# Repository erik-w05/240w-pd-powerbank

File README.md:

!WORK IN PROGRESS, NOT YET READY FOR PRODUCTION!

# 240w-pd-powerbank
A 2-14S USB-C powerbank Hardware and Software Project, which is capable of charging and discharging at 48V@5A, which is the maximum power the USB-C PD 3.2 EPR standard supports.

The design is based on the BQ25756 4-Switch (bidirectional) Buck-Boost Charge-IC and the TPS26750 USB-C PD-Controller. Even though both of these Chips could work together standalone, the RP2354 MCU is used to control the PD-negotiation and Charger-Operation, to expand the functionality.

# Features

PCB:

- 100x80mm Board Size with 4x M3 Mounting Holes

- 6 Layer Board with sensitive signals on Layer 1 and 6

- 2oz outer copper and 1oz Inner Copper possible for improved thermal performance

Power:

- USB-PD EPR 3.2 Protocol with 48V/5A, PPS and AVS

- Dead-battery support (Powerup from 5V)

- BQ25756 4-Switch Buck-Boost Controller capable of bidirectional Buck/Boost

- 2S-14S battery support, recommended for 48V@5A PD EPR is 8S-14S (14S is most efficient)

- 5A input current through USB-C and 10A discharge current max from the battery

- LMR38010 Buck Converter that generates 3.3V from 4.2-58.8V

- 7V boost converter for Gate Drive Supply

Human-Machine Interface (HMI)
- SPI Header for one Display
- 2x Buttons and 1x Rotary Encoder for User Interface Navigation
- 1x Neopixel LED for Status Indication
- Buzzer for User Feedback and Alerting

# Cost

On JLCPCB the board itself costs about 100€/5 Pieces and the components are about 100€ per board. If you want to get the board assembled, the cost will be very high. The bulk of the cost comes from assembly because of the use of mostly non-basic parts.

# My Motivation:

My old powerbank broke a couple of months ago and I always wanted to make one myself. And I also noticed, that such an Product didn't yet exist on the market, so I decided to make the first.

Inspiration:

Thanks for Theo Heng for giving me the idea and orientation on how to implement it.
https://github.com/theohg/PD240W

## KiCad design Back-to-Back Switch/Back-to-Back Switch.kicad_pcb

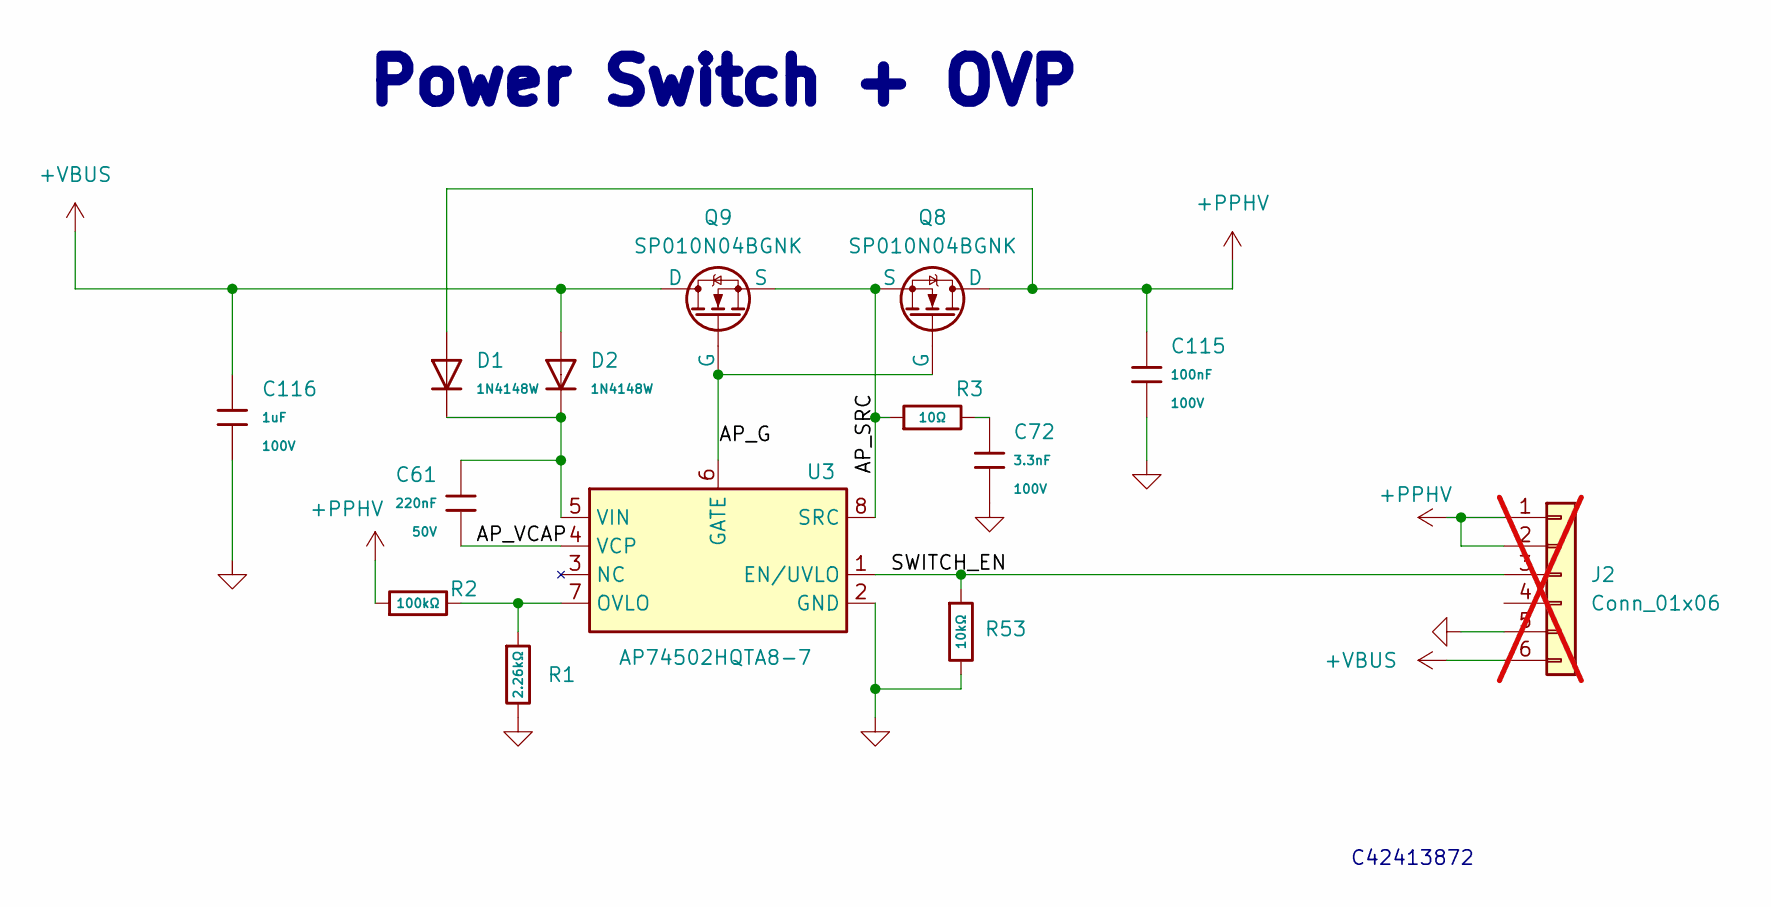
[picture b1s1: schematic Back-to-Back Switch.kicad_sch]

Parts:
C61: 220nF; C_0603_1608Metric; Voltage Rated 50V; Tolerance ±10%; Manufacturer Part Number CC0603KRX7R9BB224; LCSC C107083
C72: 3.3nF; C_0603_1608Metric; Voltage Rated 100V; Tolerance ±10%; LCSC C388015
C115: 100nF; C_0603_1608Metric; Voltage Rated 100V; Tolerance ±10%; LCSC C15725
C116: 1uF; C_0805_2012Metric; Voltage Rated 100V; Tolerance ±10%; LCSC C5370002
D1, D2: 1N4148W; D_SOD-123; Forward Voltage (Vf@If) 1.25V@150mA; Reverse Voltage (Vr) 100V; Part 1N4148W; LCSC C7420318
J2: Conn_01x06; PinHeader_1x06_P2.54mm_Vertical; not fitted
Q8, Q9: SP010N04BGNK; PDFN-8_L5.8-W5.0-P1.27-LS6.1-BL; LCSC C22466791
R1: 2.26kΩ; R_0603; Overload Voltage (Max) 75V; Tolerance ±1%
R2: 100kΩ; R_0603; Overload Voltage (Max) 75V; Tolerance ±1%; Part 0603WAF1003T5E; LCSC C25803
R3: 10Ω; R_0603; Overload Voltage (Max) 75V; Tolerance ±1%; Part 0603WAF100JT5E; LCSC C22859
R53: 10kΩ; R_0603_1608Metric; Overload Voltage (Max) 75V; Tolerance ±1%; LCSC C25804
U3: AP74502HQTA8-7; AP74502HQTA87

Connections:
+PPHV: C115.1, D1.2, J2.1, J2.2, Q8.5 (D), R2.1
+VBUS: C116.1, D2.2, J2.6, Q9.5 (D)
/AP_G: Q8.4 (G), Q9.4 (G), U3.6 (GATE)
/AP_SRC: Q8.1 (S), Q8.2 (S), Q8.3 (S), Q9.1 (S), Q9.2 (S), Q9.3 (S), R3.1, U3.8 (SRC)
/AP_VCAP: C61.2, U3.4 (VCP)
/SWITCH_EN: J2.3, R53.1, U3.1 (EN/UVLO)
GND: C72.2, C115.2, C116.2, J2.5, R1.2, R53.2, U3.2 (GND)
unnamed: C72.1, R3.2
unnamed: R1.1, R2.2, U3.7 (OVLO)
unnamed: C61.1, D1.1, D2.1, U3.5 (VIN)

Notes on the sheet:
C42413872
Power Switch + OVP

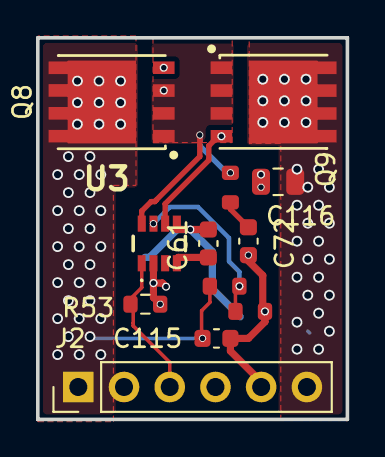
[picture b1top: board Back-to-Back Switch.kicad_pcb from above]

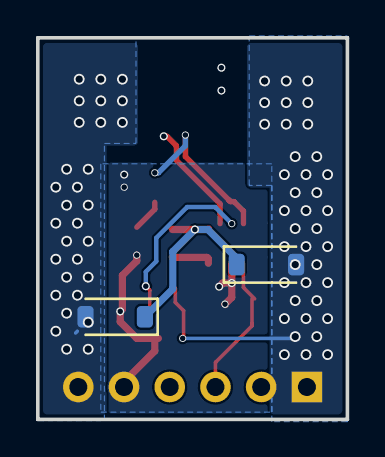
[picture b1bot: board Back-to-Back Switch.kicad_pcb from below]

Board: 4 copper layers, 17.2 x 21.2 mm, 14 parts (2 on the bottom side), 10 nets.

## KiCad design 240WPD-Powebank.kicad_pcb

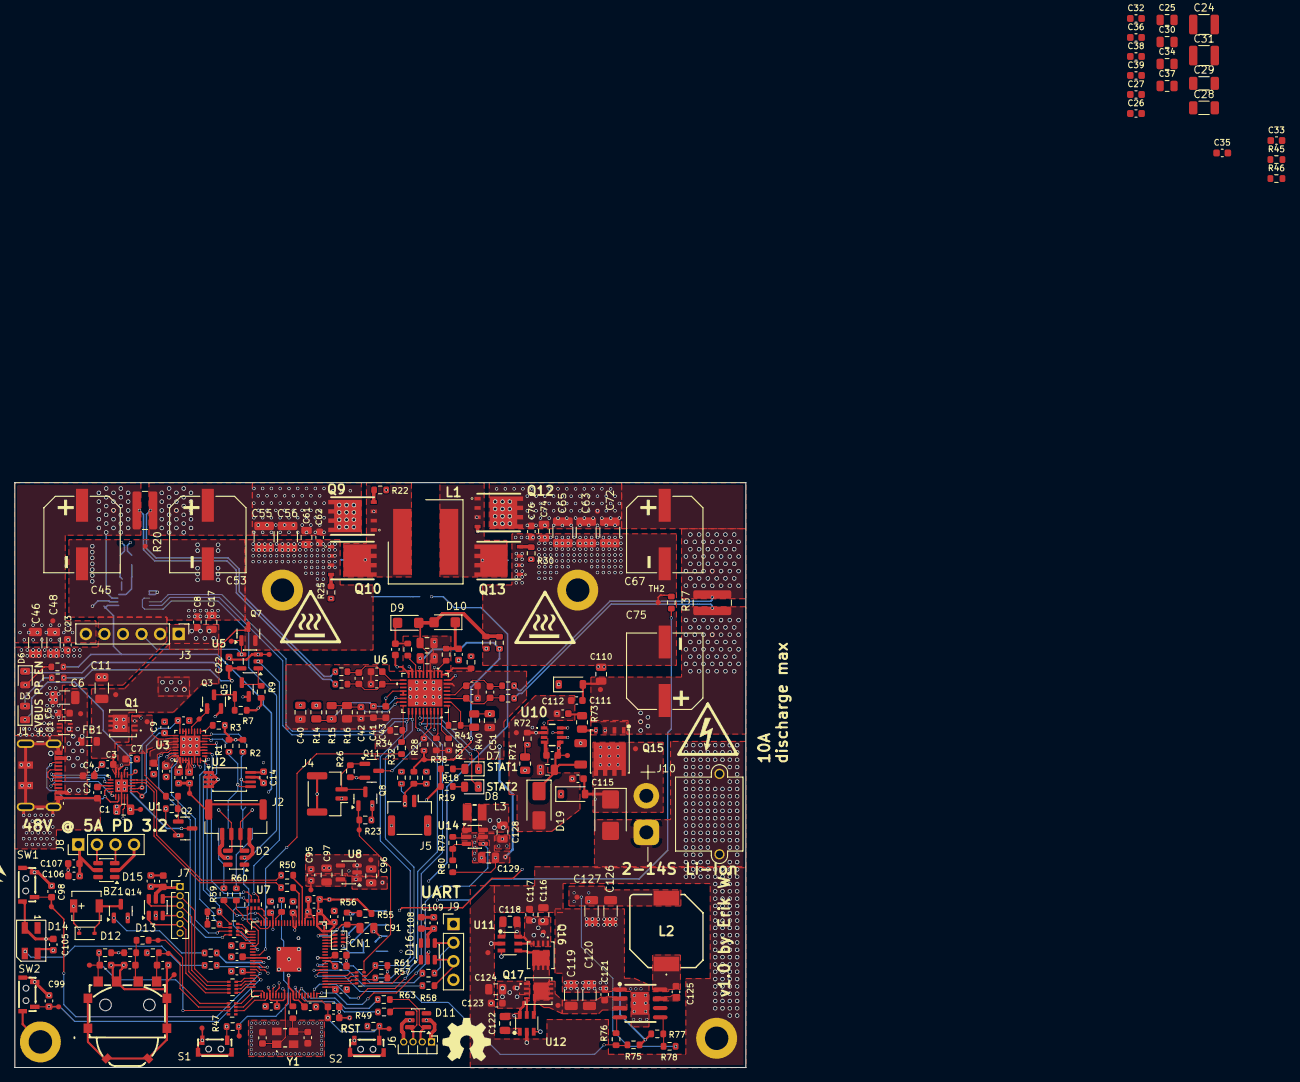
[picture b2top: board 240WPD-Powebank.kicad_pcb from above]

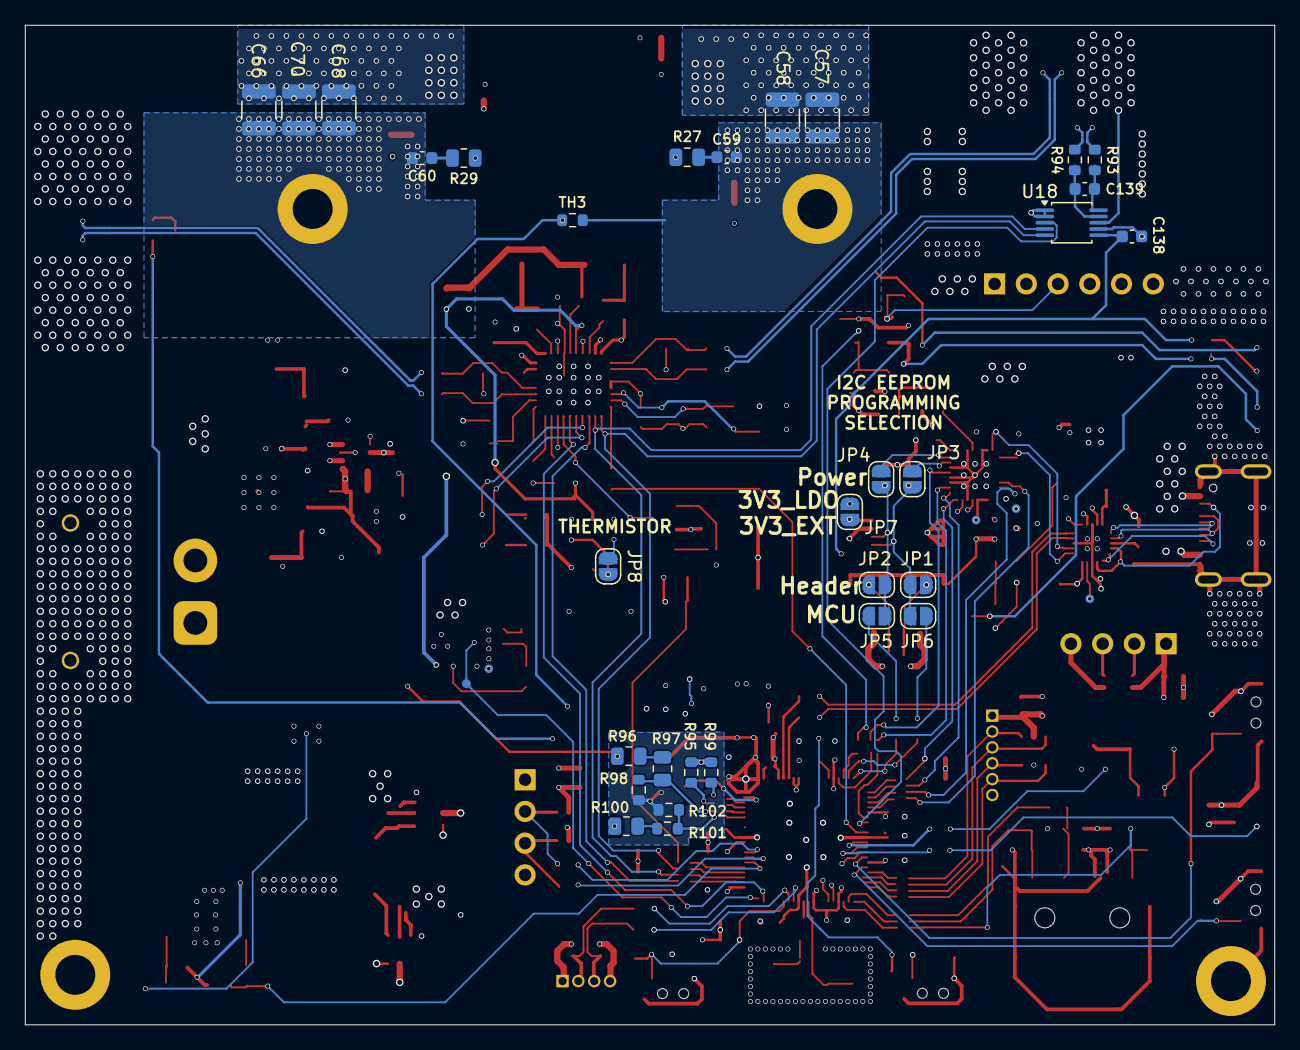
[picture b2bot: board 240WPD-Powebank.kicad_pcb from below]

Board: 6 copper layers, 100.0 x 80.0 mm, 362 parts (43 on the bottom side), 190 nets.

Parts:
BZ1: Buzzer; BUZ-SMD_L4.0-W4.0-P3.50-L
C1, C17, C25, C40, C51, C61, C74, C96, C97, C110, C114, C116, C118, C122, C124: 1uF; C_0805_2012Metric
C2, C3, C7, C8, C14, C22, C23, C32, C41, C42, C43, C49, C52, C54, C62, C64, C69, C73, C79, C80, C81, C83, C84, C85, C87, C89, C90, C92, C93, C94, C98, C99, C101, C102, C103, C104, C105, C107, C109, C111, C115, C117, C121, C123, C125, C138, C139: 100nF; C_0603_1608Metric
C4, C5: 10nF; C_0603_1608Metric
C6, C11, C29, C46, C48, C119, C120: 4.7uF; C_1206_3216Metric
C9, C10, C27: 220pF; C_0603_1608Metric
C12, C13, C15, C16, C78, C95: 10uF; C_0603_1608Metric
C24, C55, C56, C57, C58, C63, C65, C66, C68, C70, C72: 10uF; C_1210_3225Metric
C26, C50, C71: 470nF; C_0603_1608Metric
C28, C126, C127: 22uF; C_1206_3216Metric
C30, C44, C47, C91: 4.7uF; C_0805_2012Metric
C31: 4.7uF; C_1210_3225Metric
C33, C76: 100pF; C_0603_1608Metric
C34, C128, C129: 10uF; C_0805_2012Metric
C35, C113: 220nF; C_0603_1608Metric
C36, C77, C82: 15pF; C_0603_1608Metric
C37: 220nF; C_0805_2012Metric
C38, C112: 47nF; C_0603_1608Metric
C39: 3.3nF; C_0603_1608Metric
C45, C53, C67, C75: 100uF 80V ALU Polymer; CAP-SMD_BD10.0-L10.3-W10.3-FD-1
C59, C60: 33pF; C_0603_1608Metric
C86, C88, C100, C106, C108: 1uF; C_0603_1608Metric
CN1: C_Network_4x0402; C_Array_Concave_4x0402
D1: TVS5200VEBR; UQFN-6-FN-HR_VEB
D2, D11, D13, D15, D16: USBLC6-4SC6; SOT-23-6
D3: Red; LED_0805_2012Metric
D6: Blue; LED_0805_2012Metric
D7: Green; LED_0805_2012Metric
D8: Yellow; LED_0805_2012Metric
D9, D10: V1FM10-M3/H; D_SMF
D12: BAV21WS; D_SOD-323
D14: SK6812MINI; LED_SK6812MINI_PLCC4_3.5x3.5mm_P1.75mm
D17, D18: 1N4148W; D_SOD-123
D19: 1SMA4760A; D_SMA
D20: SMBJ64A; D_SMB
FB1: FerriteBead; FB_0805
H1, H2, H3, H4: MountingHole_Pad; MountingHole_3.2mm_M3_DIN965_Pad
J1: USB 2.0, 5A PD; DX07S016JA1R1500
J2: JST-GH 4-Pin; JST_GH_BM04B-GHS-TBT_1x04-1MP_P1.25mm_Vertical
J3: HTSW-106-07-G-S; PinHeader_1x06_P2.54mm_Vertical
J4, J5: JST-GH 2Pin; JST_GH_BM02B-GHS-TBT_1x02-1MP_P1.25mm_Vertical
J6: 1x4 1.27mm Pins; PinHeader_1x04_P1.27mm_Horizontal
J7: 1x6 1.27mm Pin Header; PinHeader_1x06_P1.27mm_Vertical
J8, J9: 1x4 2.54mm Pins; PinHeader_1x04_P2.54mm_Vertical
J10: XT30PW-M; AMASS_XT30PW-M_1x02_P2.50mm_Horizontal
JP1, JP2, JP3, JP4, JP5, JP6, JP7, JP8: Jumper_2_Open; SolderJumper-2_P1.3mm_Open_RoundedPad1.0x1.5mm
L1: 10uH, 17.2A; L_Wurth_WE-XHMI-1010P
L2: 33uH, 2.5A, 79mOhm; WE-PD_1050
L3: 10uH 1.2A 330mΩ; IND-SMD_L2.5-W2.0
NT1, NT2, NT3, NT4, NT7, NT8, NT9, NT10: NetTie_2; NetTie-2_SMD_Pad0.2mm
Q1, Q16, Q17: AONR62818; DFN3.3x3.3_8L_EP1_S_AOS
Q2, Q3, Q5, Q7, Q11, Q14: HL3416; Q_SOT-23
Q8: HL3415A; Q_SOT-23
Q9, Q10, Q12, Q13: BSC070N10LS5ATMA1; PG-TDSON-8-5
Q15: XRS100N12HF; XRS100N12HF_TDSON-8_L5.9-W5.2-P1.27-BL-1
R1, R2, R95, R99: 4.7kΩ; R_0603_1608Metric
R3, R7, R9, R23, R26, R28, R42, R49, R61, R62, R63, R64, R68, R69, R70, R77: 10kΩ; R_0603_1608Metric
R4, R5, R34, R98, R102: 100kΩ; R_0603_1608Metric
R6, R47, R48: 1kΩ; R_0603_1608Metric
R11, R18, R66: 330Ω; R_0603_1608Metric
R12, R13, R22, R24, R25, R30, R31, R32, R33: 0Ω; R_0603_1608Metric
R14, R71, R96, R97, R100: 1MΩ; R_0805_2012Metric
R15: 383kΩ; R_0805_2012Metric
R16: 26.1kΩ; R_0805_2012Metric
R17, R21, R35, R39: 10Ω; R_0603_1608Metric
R19, R59, R60: 680Ω; R_0603_1608Metric
R20, R37: 5mΩ; R_1020_2550Metric
R27, R29: 0Ω; R_0805_2012Metric
R36: 3.6kΩ; R_0603_1608Metric
R38: 5kΩ; R_0603_1608Metric
R40: 249kΩ; R_0805_2012Metric
R41: 6.6kΩ; R_0603_1608Metric
R43: 5.23kΩ; R_0603_1608Metric
R44: 30.1kΩ; R_0603_1608Metric
R45: 13,6kΩ; R_0603_1608Metric
R46: 9,4kΩ; R_0603_1608Metric
R50, R51, R54, R93, R94: 27Ω; R_0603_1608Metric
R52, R53: 100Ω; R_0603_1608Metric
R55: 200Ω; R_0603_1608Metric
R56: 1Ω; R_0603_1608Metric
R57, R58, R65: 220Ω; R_0603_1608Metric
R67: 33kΩ; R_0603_1608Metric
R72: 20kΩ; R_0603_1608Metric
R73: 10Ω; R_0805_2012Metric
R74: 10kΩ; R_1206
R75: 49.9Ω; R_0603_1608Metric
R76: 15kΩ; R_0603_1608Metric
R78: 24kΩ; R_0603_1608Metric
R79: 62kΩ; R_0603_1608Metric
R80: 470kΩ; R_0603_1608Metric
R101: 750kΩ; R_0603_1608Metric
RN1, RN3, RN4, RN5: 4x27Ω 0402; R_Array_Concave_4x0402
RN2: 27Ω; R_Array_Concave_4x0402
S1, S2: 1TS003B-XXXX-3500A-CT; SW-SMD_1TS003B-XXXX-3500A-CT
SW1, SW2: SW-SMD_1TS003B-XXXX-3500A-CT
TH2, TH3: 10k B3950 NTC; R_0603_1608Metric
TP1, TP2, TP3, TP4, TP5, TP6, TP7, TP8, TP9, TP10, TP11, TP12, TP13, TP14, TP15, TP16, TP17, TP18, TP19, TP20, TP21, TP22, TP23, TP24, TP25, TP26, TP27, TP28, TP29, TP30, TP31, TP32, TP33, TP34, TP35, TP36, TP37, TP38, TP39, TP40, TP41, TP42, TP43, TP44, TP45, TP46, TP47, TP48, TP49, TP50, TP51, TP52: TP_0.7mm
U1: TPD4S480RUKR; QFN40P300X300X80-21N-D
U2: M24512E-FDW6TP; TSSOP-8_4.4x3mm_P0.65mm
U3: TPS26750SRSMR; VQFN-32-1EP_4x4mm_P0.4mm_EP2.8x2.8mm
U5: 74LVC1G08SE-7; SOT-23-5
U6: BQ25756RRVR; VQFN36_RRV_TEX-M
U7: RP2354B; QFN-80-1EP_10x10mm_P0.4mm_EP3.4x3.4mm
U8: TLV71311PDBV; SOT-23-5
U9: SIQ-02FVS3; SW-SMD_SIQ-02FVS3_1
U10: AP74502QTA8-7; AP74502HQTA87
U11, U12: MX74700T; SOT-23-6_L2.9-W1.6-P0.95-LS2.9-BL
U13: LMR38010SDDAR; SOIC-8_L4.9-W3.9-P1.27-LS6.0-BL-EP-1
U14: TLV61046ADB; SOT-23-6
U18: INA238; TSSOP-10_3x3mm_P0.5mm
Y1: ABM8-272-T3

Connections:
7V_EN: TP37.1 (1_1), U7.40 (GPIO32), U14.4 (EN)
+1.1V: C92.1, C93.1, C94.1, C95.1, C97.1, TP22.1 (1_1), U7.10 (DVDD), U7.32 (DVDD), U7.51 (DVDD), U8.5 (OUT)
+1.5V_LDO: C15.1, TP6.1 (1_1), U3.2 (ADCIN1), U3.3 (ADCIN2), U3.4 (LDO_1V5)
+3.3V: BZ1.1 (+), C12.1, C78.1, C79.1, C80.1, C81.1, C83.1, C84.1, C85.1, C87.1, C89.1, C90.1, C96.1, C100.1, C101.1, C105.1, C106.1, C107.1, C108.1, C109.1, C126.1, C127.1, C128.1, C138.1, D11.5 (VBUS), D12.1, D13.5 (VBUS), D14.4 (VDD), D15.5 (VBUS), D16.5 (VBUS), J6.4, J7.1, J8.1, J9.1, L2.2, L3.1, Q8.2 (S), R11.2, R18.1, R19.1, R23.2, R49.1, R55.1, R61.1, R62.1, R63.1, R64.1, R68.1, R69.1, R70.1, R78.1, TP8.1 (1_1), TP20.1 (1_1), TP21.1 (1_1), TP38.1 (1_1), U3.32 (VIN_3V3), U7.5 (IOVDD), U7.15 (IOVDD), U7.24 (IOVDD), U7.29 (IOVDD), U7.41 (IOVDD), U7.50 (IOVDD), U7.60 (IOVDD), U7.61 (VREG_AVDD), U7.68 (USB_OTP_VDD), U7.69 (QSPI_IOVDD), U7.76 (IOVDD), U8.1 (IN), U8.3 (EN), U14.6 (VI), U18.6 (VS)
+3.3V_EEPROM: C14.1, D2.5 (VBUS), J2.1, JP7.1 (A), U2.8 (VCC)
+3.3V_LDO: C1.1, C13.1, C22.2, JP7.2 (B), R1.1, R2.1, R3.1, R6.2, R7.1, R9.1, TP7.1 (1_1), U1.10 (VPWR), U3.1 (LDO_3V3), U5.5 (VCC)
+7V: C129.1, R12.1, R80.1, TP16.1 (1_1), U14.5 (VOUT)
+PPHV: C23.1, C40.1, C43.1, C45.1, C46.1, C48.1, J3.6, NT1.1, NT7.1, R14.1, R20.1, TP17.1 (1_1), TP47.1 (1_1), U6.32 (VAC_1), U6.33 (VAC_2), U18.8 (Vbus)
+PPHV_C: C53.1, C55.1, C56.1, C57.1, C58.1, C61.1, C62.1, NT2.2, NT8.2, Q9.5 (D), R20.2, TP48.1 (1_1)
+REGN: C47.1, R13.1, R28.1, R43.1, TP15.1 (1_1), U6.24 (REGN)
+VBAT: C115.1, D17.2, D20.1, J10.2 (+), Q15.5 (D), R71.1, TP35.1 (1_1)
+VBAT-Divided: CN1.2 (C1), R97.2, R98.1
+VBUS: C3.1, C8.1, C11.1, C17.1, C122.2, C123.1, C124.1, FB1.2, J3.1, Q1.5 (D), Q17.1 (S), Q17.2 (S), Q17.3 (S), R100.1, TP4.1 (1_1), TP41.1 (1_1), TP42.1 (1_1), U1.20 (VBUS), U12.3 (EN), U12.6 (ANODE)
+VBUS_C: C4.1, C5.1, C6.1, D1.1 (K), FB1.1, J1.A4 (VBUS), J1.B4 (VBUS), TP3.1 (1_1)
+VBUS_Divided: CN1.1 (C1), R101.2, R102.1
+VBUS_LV: C7.1, Q1.1 (S), Q1.2 (S), Q1.3 (S), R4.1, TP5.1 (1_1), U1.19 (VBUS_LV), U3.26 (VBUS), U3.27 (VBUS)
+VCHARGE: C51.1, C75.1, C110.1, C111.1, C116.1, C117.1, C118.2, D18.2, NT4.2, Q15.1 (S), Q15.2 (S), Q15.3 (S), Q16.1 (S), Q16.2 (S), Q16.3 (S), R37.2, R40.1, R96.1, TP18.1 (1_1), TP39.1 (1_1), TP40.1 (1_1), TP49.1 (1_1), U10.8 (SRC), U11.3 (EN), U11.6 (ANODE)
+VCHARGE_C: C63.1, C65.1, C66.1, C67.1, C68.1, C70.1, C72.1, C74.1, C76.1, NT3.1, Q12.5 (D), R37.1, TP46.1 (1_1), TP50.1 (1_1)
/3V3, 7V Generation/3V3_SW: C125.1, L2.1, U13.8 (SW)
/3V3, 7V Generation/+BUCK_VIN: C119.1, C120.1, C121.1, Q16.5 (D), Q17.5 (D), TP43.1 (1_1), U11.4 (CATHODE), U12.4 (CATHODE), U13.2 (EN), U13.3 (VIN)
/3V3, 7V Generation/ORING_G1: Q16.4 (G), U11.5 (GATE)
/3V3, 7V Generation/ORING_G2: Q17.4 (G), U12.5 (GATE)
/3V3, 7V Generation/VCAP_ORING1: C118.1, U11.1 (VCAP)
/3V3, 7V Generation/VCAP_ORING2: C122.1, U12.1 (VCAP)
/Battery Port/AP_BAT_VCAP: C113.2, U10.4 (VCP)
/Battery Port/AP_BAT_VIN: C113.1, C114.1, D19.1, R74.2, TP34.1 (1_1), U10.1 (EN/UVLO), U10.5 (VIN)
/Battery Port/AP_VIN_R: D17.1, D18.1, R74.1
/Battery Port/BAT_G: Q15.4 (G), R73.2, U10.6 (GATE)
/Charger/BTST1: C54.2, D9.1 (K), R24.1
/Charger/BTST2: C64.2, D10.1 (K), R31.1
/Charger/DRV_SUP: C44.1, D9.2 (A), D10.2 (A), R12.2, R13.2, U6.23 (DRV_SUP)
/Charger/HIDRV1: R22.2, U6.27 (HIDRV1)
/Charger/HIDRV1_R: Q9.4 (G), R22.1
/Charger/HIDRV2: R33.2, U6.19 (HIDRV2)
/Charger/HIDRV2_R: Q12.4 (G), R33.1
/Charger/LODRV1: R25.2, U6.25 (LODRV1)
/Charger/LODRV1_R: Q10.4 (G), R25.1
/Charger/LODRV2: R30.2, U6.21 (LODRV2)
/Charger/LODRV2_R: Q13.4 (G), R30.1
/Charger/SR_N: NT4.1, R39.1
/Charger/SR_P: NT3.2, R35.1
/Charger/SW1: C54.1, L1.1, Q9.1 (S), Q9.2 (S), Q9.3 (S), Q10.5 (D), R27.1, U6.28 (SW1)
/Charger/SW2: C64.1, L1.2, Q12.1 (S), Q12.2 (S), Q12.3 (S), Q13.5 (D), R29.1, U6.18 (SW2)
/Charger/TS: J5.2, JP8.2 (B), R43.2, R44.1, U6.8 (TS)
/MCU and HMI/BUTTON_1: C98.1, SW1.1, TP29.1 (1_1), U7.14 (GPIO15)
/MCU and HMI/BUTTON_2: C99.1, SW2.1, TP30.1 (1_1), U7.16 (GPIO16)
/MCU and HMI/BUZZER_PWM: R65.1, U7.11 (GPIO12)
/MCU and HMI/BUZZER_PWM_R: Q14.1 (G), R65.2
/MCU and HMI/ENCODER_A: C102.1, R68.2, RN5.6 (R3.2), TP26.1 (1_1), U9.A
/MCU and HMI/ENCODER_B: C103.1, R69.2, RN5.7 (R2.2), TP27.1 (1_1), U9.B
/MCU and HMI/ENCODER_S: R67.1, RN5.5 (R4.2), TP28.1 (1_1)
/MCU and HMI/SPI_CS: D13.4 (I/O3), J7.2, RN4.5 (R4.2)
/MCU and HMI/SPI_RX: D13.1 (I/O1), J7.5, RN4.8 (R1.2)
/MCU and HMI/SPI_SCLK: D13.6 (I/O4), J7.3, RN4.6 (R3.2)
/MCU and HMI/SPI_TX: D13.3 (I/O2), J7.4, RN4.7 (R2.2)
/MCU and HMI/SWCLK: D11.6 (I/O4), J6.3, R53.1
/MCU and HMI/SWCLK_CH32: D15.3 (I/O2), J8.3
/MCU and HMI/SWDIO: D11.1 (I/O1), J6.2, R52.1
/MCU and HMI/SWIO_CH32: D15.4 (I/O3), J8.2
/MCU and HMI/UART1_RX: D16.4 (I/O3), J9.2, R57.2
/MCU and HMI/UART1_TX: D16.3 (I/O2), J9.3, R58.2
/MCU and HMI/USB_D+_R_P: R51.2, U7.67 (USB_DP)
/MCU and HMI/USB_D-_R_N: R50.2, U7.66 (USB_DM)
/MCU and HMI/WS2812B_PWM: R66.1, U7.12 (GPIO13)
/MCU and HMI/WS2812B_PWM_R: D14.3 (DIN), R66.2
/MCU and HMI/XIN: C82.1, U7.30 (XIN), Y1.1
/MCU and HMI/XOUT: C77.1, R48.1, Y1.3
/MCU and HMI/XOUT_R: R48.2, U7.31 (XOUT)
/MCU and HMI/~QSPI_SS: R47.1, R54.1, TP24.1 (1_1)
/MCU and HMI/~RESET: C86.1, C88.1, R49.2, S2.1 (A), TP25.1 (1_1), U7.35 (RUN)
/Sensing/VIN+: C139.1, R93.2, U18.10 (Vin+)
/Sensing/VIN-: C139.2, R94.1, U18.9 (Vin-)
/USB-C/CC1: C10.1, TP1.1 (1_1), U1.12 (CC1), U3.24 (CC1)
/USB-C/CC2: C9.1, TP9.1 (1_1), U1.11 (CC2), U3.25 (CC2)
/USB-C/EPR_EN: TP13.1 (1_1), U1.16 (EPR_EN), U3.7 (GPIO2)
/USB-C/I2CC_IRQ: R3.2, U3.17 (*I2CC_IRQ)
/USB-C/I2CC_SCL: JP4.2 (B), U3.16 (I2CC_SCL)
/USB-C/I2CC_SCL_EEPROM: JP2.2 (B), JP4.1 (A), JP5.1 (A), R2.2, U2.6 (SCL)
/USB-C/I2CC_SCL_EXT: D2.3 (I/O2), J2.3 (Pin_1), JP2.1 (A)
/USB-C/I2CC_SDA: JP3.2 (B), U3.15 (I2CC_SDA)
/USB-C/I2CC_SDA_EEPROM: JP1.2 (B), JP3.1 (A), JP6.1 (A), R1.2, U2.5 (SDA)
/USB-C/I2CC_SDA_EXT: D2.4 (I/O3), J2.2, JP1.1 (A)
/USB-C/POWER_PATH_EN: Q3.1 (G), TP10.1 (1_1), U3.20 (POWER_PATH_EN)
/USB-C/PP5V: C16.1, U3.28 (PP5V), U3.29 (PP5V)
/USB-C/SWITCH_EN: J3.3, Q7.1 (G), TP2.1 (1_1), U5.4
/USB-C/SWITCH_EN_PDIC: Q5.3 (D), R9.2, U5.1
/USB-C/USB_D_C_N: J1.A7 (D-), J1.B7 (D-), U1.2 (USB_D-_C)
/USB-C/USB_D_C_P: J1.A6 (D+), J1.B6 (D+), U1.1 (USB_D+_C)
/USB-C/VBIAS: C2.1, U1.3 (VBIAS)
/USB-C/~FLT: TP14.1 (1_1), U1.9 (~FLT), U3.5 (GPIO0)
AC_N: NT2.1, NT8.1, R21.1, R94.2
AC_P: NT1.2, NT7.2, R17.1, R93.1
ADC_VREF: R55.2, R56.2, R95.1, R99.1
BQ25756_INT: RN1.5 (R4.2), U6.3 (~INT)
BQ25756_PGn: U6.6 (~PG), U7.39 (GPIO31)
GND: C1.2, C2.2, C3.2, C4.2, C5.2, C6.2, C7.2, C8.2, C9.2, C10.2, C11.2, C12.2, C13.2, C14.2, C15.2, C16.2, C17.2, C22.1, C23.2, C40.2, C41.2, C42.2, C43.2, C44.2, C45.2, C46.2, C47.2, C48.2, C49.2, C51.2, C52.2, C53.2, C55.2, C56.2, C57.2, C58.2, C59.2, C60.2, C61.2, C62.2, C63.2, C65.2, C66.2, C67.2, C68.2, C69.2, C70.2, C72.2, C73.2, C74.2, C75.2, C76.2, C77.2, C78.2, C79.2, C80.2, C81.2, C82.2, C83.2, C84.2, C85.2, C86.2, C87.2, C88.2, C89.2, C90.2, C91.2, C92.2, C93.2, C94.2, C95.2, C96.2, C97.2, C98.2, C99.2, C100.2, C101.2, C102.2, C103.2, C104.2, C105.2, C106.2, C107.2, C108.2, C109.2, C110.2, C111.2, C112.2, C114.2, C115.2, C116.2, C117.2, C119.2, C120.2, C121.2, C123.2, C124.2, C126.2, C127.2, C128.2, C129.2, C138.2, D1.4 (A), D2.2 (GND), D11.2 (GND), D13.2 (GND), D14.2 (VSS), D15.2 (GND), D16.2 (GND), D19.2, D20.2, H1.1 (1_1), H2.1 (1_1), H3.1 (1_1), H4.1 (1_1), J1.A1 (GND), J1.B1 (GND), J1.SH (SHIELD), J2.4 (Pin_2), J2.MP1, J2.MP2, J3.2, J4.1, J4.MP1, J4.MP2, J5.MP1, J5.MP2, J6.1, J7.6, J8.4, J9.4, J10.1 (-), J10.3, J10.4, NT9.1, NT10.1, Q2.2 (S), Q3.2 (S), Q5.2 (S), Q7.2 (S), Q10.1 (S), Q10.2 (S), Q10.3 (S), Q11.2 (S), Q13.1 (S), Q13.2 (S), Q13.3 (S), Q14.2 (S), R5.2, R16.2, R26.2, R34.2, R36.2, R38.2, R42.2, R44.2, R72.2, R75.2, R77.2, R79.2, R98.2, R102.2, S1.2 (B), S1.MP, S2.2 (B), S2.MP, SW1.2, SW1.MP (B), SW2.2, SW2.MP (B), TP11.1 (1_1), TP12.1 (1_1), TP23.1 (1_1), TP31.1 (1_1), TP32.1 (1_1), TP33.1 (1_1), TP36.1 (1_1), TP44.1 (1_1), TP45.1 (1_1), TP51.1 (1_1), TP52.1 (1_1), U1.8 (GND), U1.13 (GND), U1.18 (GND), U1.21 (EP), U2.1 (A0), U2.2 (A1), U2.3 (A2), U2.4 (VSS), U2.7 (WP), U3.6 (GPIO1), U3.11 (GND), U3.12 (GND), U3.14 (GND), U3.19 (GND), U3.22 (GPIO4/USB_P/LD1), U3.23 (GPIO5/USB_N/LD2), U3.33 (GND), U5.3 (GND), U6.17 (PGND_1), U6.22 (PGND_2), U6.37 (PGND_3), U7.62 (VREG_PGND), U7.65 (VREG_FB), U7.81 (GND), U8.2 (GND), U9.C, U9.MP, U10.2 (GND), U11.2 (GND), U12.2 (GND), U13.1 (GND), U13.9 (EP), U14.2 (GND), U18.1 (A1), U18.2 (A0), U18.7 (GND), Y1.2, Y1.4
I2C0_SCL: R64.2, RN3.2 (R2.1), U3.9 (I2CT_SCL)
I2C0_SDA: R62.2, RN3.1 (R1.1), U3.8 (I2CT_SDA)
I2C1_SCL: R61.2, RN1.7 (R2.2), U6.1 (SCL), U18.5 (SCL)
I2C1_SCL_MUX: JP5.2 (B), R60.2
I2C1_SDA: R63.2, RN1.6 (R3.2), U6.2 (SDA), U18.4 (SDA)
I2C1_SDA_MUX: JP6.2 (B), R59.2
INA_ALERT: U7.7 (GPIO9), U18.3 (~Alert)
NTC1: CN1.4 (C3), R99.2, TH3.1
NTC2: CN1.3 (C2), R95.2, TH2.1
unnamed: BZ1.2 (-), D12.2, Q14.3 (D)
unnamed: C59.1, R27.2
unnamed: C60.1, R29.2
unnamed: C104.1, R67.2, R70.2, U9.S
unnamed: C112.1, R73.1
unnamed: D3.2, R6.1
unnamed: D6.2, R11.1
unnamed: D7.2, R18.2
unnamed: D8.2, R19.2
unnamed: J1.A5 (CC1), U1.4 (C_CC1), U1.7 (RPD_G1)
unnamed: J1.B5 (CC2), U1.5 (C_CC2), U1.6 (RPD_G2)
unnamed: J4.2, Q8.3 (D), Q11.1 (G), R26.1
unnamed: JP8.1 (A), R42.1
unnamed: NT9.2, TH2.2
unnamed: NT10.2, TH3.2
unnamed: Q1.4 (G), U1.17 (EPR_BLK_G)
unnamed: D3.1, Q2.3 (D)
unnamed: Q2.1 (G), R4.2, R5.1
unnamed: Q3.3 (D), Q5.1 (G), R7.2
unnamed: D6.1, Q7.3 (D)
unnamed: Q11.3 (D), R28.2, U6.7 (~CE)
unnamed: R96.2, R97.1
unnamed: R100.2, R101.1
unnamed: RN1.1 (R1.1), U7.45 (GPIO36)
unnamed: RN1.2 (R2.1), U7.44 (GPIO35)
unnamed: RN1.3 (R3.1), U7.43 (GPIO34)
unnamed: RN1.4 (R4.1), U7.42 (GPIO33)
unnamed: RN2.1 (R1.1), U7.6 (GPIO8)
unnamed: RN2.2 (R2.1), U7.77 (GPIO0)
unnamed: RN2.4 (R4.1), U7.78 (GPIO1)
unnamed: RN3.8 (R1.2), U7.1 (GPIO4)
unnamed: RN3.7 (R2.2), U7.2 (GPIO5)
unnamed: RN3.6 (R3.2), U7.3 (GPIO6)
unnamed: RN3.5 (R4.2), U7.4 (GPIO7)
unnamed: RN4.1 (R1.1), U7.20 (GPIO20)
unnamed: RN4.2 (R2.1), U7.19 (GPIO19)
unnamed: RN4.3 (R3.1), U7.18 (GPIO18)
unnamed: RN4.4 (R4.1), U7.17 (GPIO17)
unnamed: RN5.2 (R2.1), U7.23 (GPIO23)
unnamed: RN5.3 (R3.1), U7.21 (GPIO21)
unnamed: RN5.4 (R4.1), U7.22 (GPIO22)
unnamed: R47.2, S1.1 (A)
unnamed: C50.2, C52.1, R21.2, U6.29 (ACN)
unnamed: C42.1, R15.2, R16.1, U6.35 (ACOV)
unnamed: C49.1, C50.1, R17.2, U6.30 (ACP)
unnamed: C41.1, R14.2, R15.1, U6.34 (ACUV)
unnamed: R24.2, U6.26 (BTST1)
unnamed: R31.2, U6.20 (BTST2)
unnamed: R40.2, R41.1, U6.12 (FB)
unnamed: R41.2, U6.11 (FBG)
unnamed: R32.2, R34.1, U6.36 (FSW_SYNC)
unnamed: R38.1, U6.9 (ICHG)
unnamed: R36.1, U6.10 (ILIM_HIZ)
unnamed: C71.2, C73.1, R39.2, U6.13 (SRN)
unnamed: C69.1, C71.1, R35.2, U6.14 (SRP)
unnamed: D7.1, U6.4 (STAT1)
unnamed: D8.1, U6.5 (STAT2)
unnamed: C91.1, R56.1, U7.59 (ADC_AVDD)
unnamed: R59.1, U7.79 (GPIO2)
unnamed: R60.1, U7.80 (GPIO3)
unnamed: R58.1, U7.47 (GPIO38)
unnamed: R57.1, U7.48 (GPIO39)
unnamed: CN1.8, U7.55 (GPIO44/ADC4)
unnamed: CN1.7, U7.56 (GPIO45/ADC5)
unnamed: CN1.6, U7.57 (GPIO46/ADC6)
unnamed: CN1.5, U7.58 (GPIO47/ADC7)
unnamed: R53.2, U7.33 (SWCLK)
unnamed: R52.2, U7.34 (SWDIO)
unnamed: R54.2, U7.75 (~QSPI_SS)
unnamed: R71.2, R72.1, U10.7 (OVLO)
unnamed: C125.2, U13.7 (BOOT)
unnamed: R77.1, R78.2, U13.5 (FB)
unnamed: R76.2, U13.4 (RT/SYNC)
unnamed: R79.1, R80.2, U14.3 (FB)
unnamed: L3.2, U14.1 (SW)
PD_GPIO6: RN3.3 (R3.1), U3.31 (GPIO6)
PD_GPIO7: RN3.4 (R4.1), U3.30 (GPIO7)
PD_GPIO11: RN2.7 (R2.2), U3.13 (GPIO11)
PWM_SYNC1: R32.1, U7.9 (GPIO11)
PWM_SYNC2: R75.1, R76.1, U7.46 (GPIO37)
SWITCH_EN_MCU: RN2.5 (R4.2), U5.2
USB_D+: R51.1, U1.14 (USB_D-)
USB_D-: R50.1, U1.15 (USB_D+)
USB_PD_IRQ: RN2.8 (R1.2), U3.10 (*I2CT_IRQ)
~CHARGER_EN: Q8.1 (G), R23.1, RN1.8 (R1.2), TP19.1 (1_1)
